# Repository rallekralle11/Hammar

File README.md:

This board is untested. Make at your own risk.

Based on the ESP wroom-32E, which also enables wifi communication.
Total size is only 97,5x55mm

Still in development, but should be functional. Use with the fysetc E4 config in marlin

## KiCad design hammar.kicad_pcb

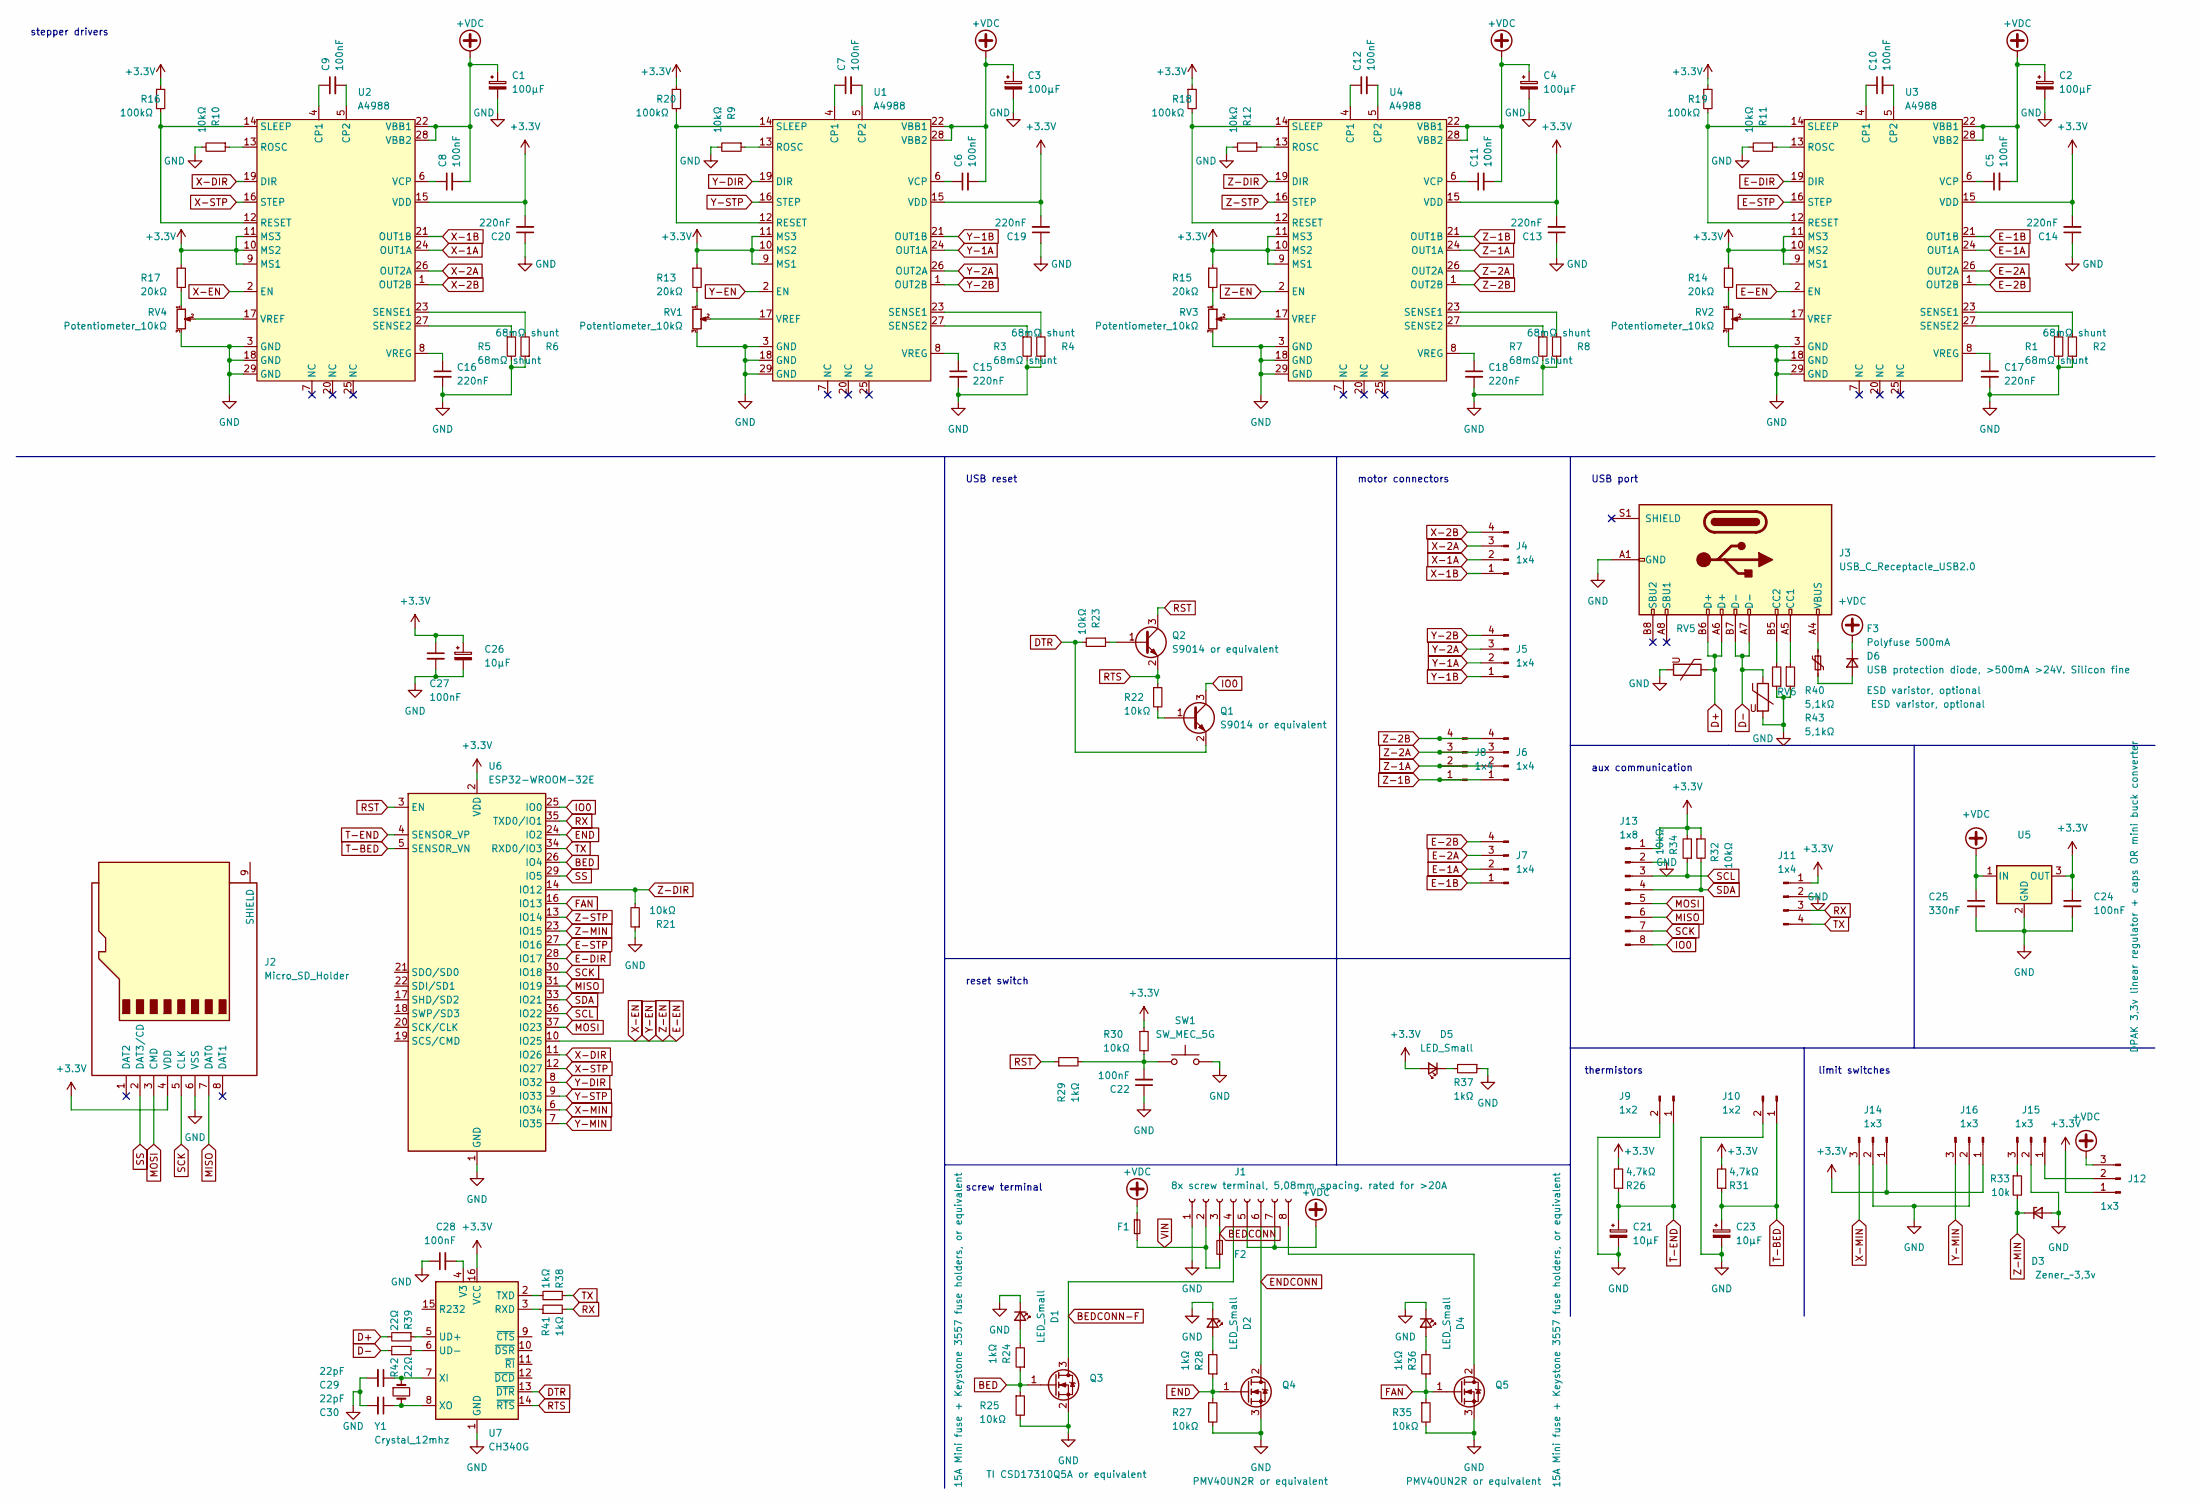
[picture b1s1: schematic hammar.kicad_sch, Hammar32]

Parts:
C1, C2, C3, C4: 100µF; CP_Elec_6.3x4.9
C5, C6, C7, C8, C9, C10, C11, C12, C22, C24, C27, C28: 100nF; C_0603_1608Metric
C13, C14, C15, C16, C17, C18, C19, C20: 220nF; C_0603_1608Metric
C21, C23, C26: 10µF; C_0805_2012Metric
C25: 330nF; C_0603_1608Metric
C29, C30: 22pF; C_0603_1608Metric
D1, D2, D4, D5: LED_Small; LED 0603 reverse mount
D3: Zener_~3,3v; D_SOD-323
D6: USB protection diode, >500mA >24V. Silicon fine; D_SOD-323
F1, F2: 15A Mini fuse + Keystone 3557 fuse holders, or eq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; mini fuse sep
F3: Polyfuse 500mA; Fuse_1206_3216Metric
J1: 8x screw terminal, 5,08mm spacing. rated for >20A; TerminalBlock_bornier-6_P5.08mm
J2: Micro_SD_Holder; microSD
J3: USB_C_Receptacle_USB2.0; USB_C_Receptacle_HRO_TYPE-C-31-M-12
J4, J5, J6, J7, J8, J11: 1x4; PinHeader_1x04_P2.54mm_Vertical
J9, J10: 1x2; PinHeader_1x02_P2.54mm_Vertical
J12, J14, J15, J16: 1x3; PinHeader_1x03_P2.54mm_Vertical
J13: 1x8; PinHeader_1x08_P2.54mm_Vertical
Q1, Q2: S9014 or equivalent; SOT-23
Q3: TI CSD17310Q5A or equivalent; 8-VSONP (5x6)
Q4, Q5: PMV40UN2R or equivalent; SOT-23
R1, R2, R3, R4, R5, R6, R7, R8: 68mΩ shunt; R_0603_1608Metric
R9, R10, R11, R12, R21, R22, R23, R25, R27, R30, R32, R34, R35: 10kΩ; R_0603_1608Metric
R13, R14, R15, R17: 20kΩ; R_0603_1608Metric
R16, R18, R19, R20: 100kΩ; R_0603_1608Metric
R24, R28, R29, R36, R37, R38, R41: 1kΩ; R_0603_1608Metric
R26, R31: 4,7kΩ; R_0603_1608Metric
R33: 10k; R_0603_1608Metric
R39, R42: 22Ω; R_0603_1608Metric
R40, R43: 5,1kΩ; R_0603_1608Metric
RV1, RV2, RV3, RV4: Potentiometer_10kΩ; Potentiometer_Bourns_3314J_Vertical
RV5, RV6: ESD varistor, optional; R_0603_1608Metric
SW1: SW_MEC_5G; SW_PUSH_6mm
U1, U2, U3, U4: A4988; QFN-28-1EP_5x5mm_P0.5mm_EP3.35x3.35mm
U5: DPAK 3,3v linear regulator + caps OR mini buck co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; mini BUCK
U6: ESP32-WROOM-32E; ESP32-WROOM-32
U7: CH340G; SOIC-16_3.9x9.9mm_P1.27mm
Y1: Crystal_12mhz; Crystal_SMD_ECS_CSM3X-2Pin_7.6x4.1mm

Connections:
+3.3V: C13.2, C14.2, C19.2, C20.2, C24.1, C26.1, C27.1, D5.2 (A), J2.4 (VDD), J11.1, J12.1, J13.1, J14.1, J16.1, R13.1, R14.1, R15.1, R16.1, R17.1, R18.1, R19.1, R20.1, R26.2, R30.1, R31.2, R32.1, R34.2, U1.9 (MS1), U1.10 (MS2), U1.11 (MS3), U1.15 (VDD), U2.9 (MS1), U2.10 (MS2), U2.11 (MS3), U2.15 (VDD), U3.9 (MS1), U3.10 (MS2), U3.11 (MS3), U3.15 (VDD), U4.9 (MS1), U4.10 (MS2), U4.11 (MS3), U4.15 (VDD), U5.3 (OUT), U6.2 (VDD), U7.16 (VCC)
+VDC: C1.1, C2.1, C3.1, C4.1, C5.2, C6.2, C8.2, C11.2, C25.1, D6.1 (K), F1.1, J1.5, J1.7, J12.3, U1.22 (VBB1), U1.28 (VBB2), U2.22 (VBB1), U2.28 (VBB2), U3.22 (VBB1), U3.28 (VBB2), U4.22 (VBB1), U4.28 (VBB2), U5.1 (IN)
BED: Q3.1 (G), R24.1, R25.1, U6.26 (IO4)
BEDCONN: F2.1, J1.3
BEDCONN-F: J1.4, Q3.3 (D)
D+: J3.A6 (D+), J3.B6 (D+), R39.2, RV5.1
D-: J3.A7 (D-), J3.B7 (D-), R42.1, RV6.1
DTR: Q1.2 (E), R23.2, U7.13 (~DTR)
E-1A: J7.2, U3.24 (OUT1A)
E-1B: J7.1, U3.21 (OUT1B)
E-2A: J7.3, U3.26 (OUT2A)
E-2B: J7.4, U3.1 (OUT2B)
E-DIR: U3.19 (DIR), U6.28 (IO17)
E-EN: U1.2 (EN), U2.2 (EN), U3.2 (EN), U4.2 (EN), U6.10 (IO25)
E-STP: U3.16 (STEP), U6.27 (IO16)
END: Q4.1 (G), R27.1, R28.1, U6.24 (IO2)
ENDCONN: J1.6, Q4.2 (D)
FAN: Q5.1 (G), R35.1, R36.1, U6.16 (IO13)
IO0: J13.8, Q1.3 (C), U6.25 (IO0)
MISO: J2.7 (DAT0), J13.6, U6.31 (IO19)
MOSI: J2.3 (CMD), J13.5, U6.37 (IO23)
unnamed: C5.1, U3.6 (VCP)
unnamed: C6.1, U1.6 (VCP)
unnamed: C7.1, U1.4 (CP1)
unnamed: C7.2, U1.5 (CP2)
unnamed: C8.1, U2.6 (VCP)
unnamed: C9.1, U2.4 (CP1)
unnamed: C9.2, U2.5 (CP2)
unnamed: C10.1, U3.4 (CP1)
unnamed: C10.2, U3.5 (CP2)
unnamed: C11.1, U4.6 (VCP)
unnamed: C12.1, U4.4 (CP1)
unnamed: C12.2, U4.5 (CP2)
unnamed: C15.1, U1.8 (VREG)
unnamed: C16.1, U2.8 (VREG)
unnamed: C17.1, U3.8 (VREG)
unnamed: C18.1, U4.8 (VREG)
unnamed: C28.2, U7.4 (V3)
unnamed: C29.1, U7.7 (XI), Y1.1
unnamed: C30.1, U7.8 (XO), Y1.2
unnamed: D1.2 (A), R24.2
unnamed: D2.2 (A), R28.2
unnamed: D4.2 (A), R36.2
unnamed: D5.1 (K), R37.2
unnamed: D6.2 (A), F3.2
unnamed: F3.1, J3.A4 (VBUS), J3.A9 (VBUS), J3.B4 (VBUS), J3.B9 (VBUS)
unnamed: J1.8, Q5.2 (D)
unnamed: J3.A5 (CC1), R43.1
unnamed: J3.B5 (CC2), R40.2
unnamed: J12.2, J15.1
unnamed: J15.3, R33.1
unnamed: Q1.1 (B), R22.2
unnamed: Q2.1 (B), R23.1
unnamed: R1.1, U3.27 (SENSE2)
unnamed: R2.2, U3.23 (SENSE1)
unnamed: R3.1, U1.27 (SENSE2)
unnamed: R4.2, U1.23 (SENSE1)
unnamed: R5.1, U2.27 (SENSE2)
unnamed: R6.2, U2.23 (SENSE1)
unnamed: R7.1, U4.27 (SENSE2)
unnamed: R8.2, U4.23 (SENSE1)
unnamed: R9.1, U1.13 (ROSC)
unnamed: R10.1, U2.13 (ROSC)
unnamed: R11.1, U3.13 (ROSC)
unnamed: R12.1, U4.13 (ROSC)
unnamed: R13.2, RV1.1
unnamed: R14.2, RV2.1
unnamed: R15.2, RV3.1
unnamed: R16.2, U2.12 (RESET), U2.14 (SLEEP)
unnamed: R17.2, RV4.1
unnamed: R18.2, U4.12 (RESET), U4.14 (SLEEP)
unnamed: R19.2, U3.12 (RESET), U3.14 (SLEEP)
unnamed: R20.2, U1.12 (RESET), U1.14 (SLEEP)
unnamed: R38.2, U7.2 (TXD)
unnamed: R39.1, U7.5 (UD+)
unnamed: R41.1, U7.3 (RXD)
unnamed: R42.2, U7.6 (UD-)
unnamed: RV1.2, U1.17 (VREF)
unnamed: RV2.2, U3.17 (VREF)
unnamed: RV3.2, U4.17 (VREF)
unnamed: RV4.2, U2.17 (VREF)
RST: Q2.3 (C), R29.1, U6.3 (EN)
RTS: Q2.2 (E), R22.1, U7.14 (~RTS)
RX: J11.3, R41.2, U6.35 (TXD0/IO1)
SCK: J2.5 (CLK), J13.7, U6.30 (IO18)
SCL: J13.3, R34.1, U6.36 (IO22)
SDA: J13.4, R32.2, U6.33 (IO21)
SS: J2.2 (DAT3/CD), U6.29 (IO5)
T-BED: C23.1, J10.1, R31.1, U6.5 (SENSOR_VN)
T-END: C21.1, J9.1, R26.1, U6.4 (SENSOR_VP)
TX: J11.4, R38.1, U6.34 (RXD0/IO3)
VIN: F1.2, F2.2, J1.2
X-1A: J4.2, U2.24 (OUT1A)
X-1B: J4.1, U2.21 (OUT1B)
X-2A: J4.3, U2.26 (OUT2A)
X-2B: J4.4, U2.1 (OUT2B)
X-DIR: U2.19 (DIR), U6.11 (IO26)
X-MIN: J14.3, U6.6 (IO34)
X-STP: U2.16 (STEP), U6.12 (IO27)
Y-1A: J5.2, U1.24 (OUT1A)
Y-1B: J5.1, U1.21 (OUT1B)
Y-2A: J5.3, U1.26 (OUT2A)
Y-2B: J5.4, U1.1 (OUT2B)
Y-DIR: U1.19 (DIR), U6.8 (IO32)
Y-MIN: J16.3, U6.7 (IO35)
Y-STP: U1.16 (STEP), U6.9 (IO33)
Z-1A: J6.2, J8.2, U4.24 (OUT1A)
Z-1B: J6.1, J8.1, U4.21 (OUT1B)
Z-2A: J6.3, J8.3, U4.26 (OUT2A)
Z-2B: J6.4, J8.4, U4.1 (OUT2B)
Z-DIR: R21.2, U4.19 (DIR), U6.14 (IO12)
Z-MIN: D3.1 (K), R33.2, U6.23 (IO15)
Z-STP: U4.16 (STEP), U6.13 (IO14)

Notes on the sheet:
USB reset
USB port
reset switch
limit switches
stepper drivers
thermistors
aux communication
motor connectors
screw terminal

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
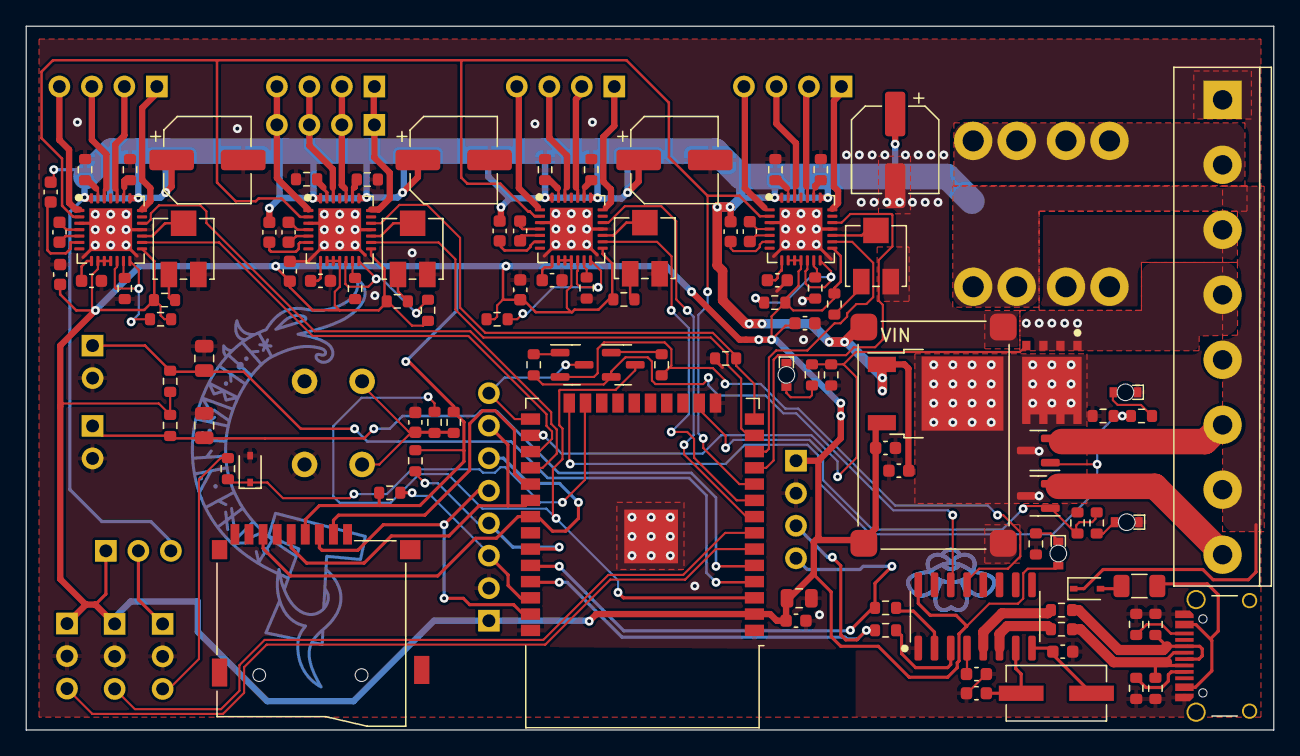
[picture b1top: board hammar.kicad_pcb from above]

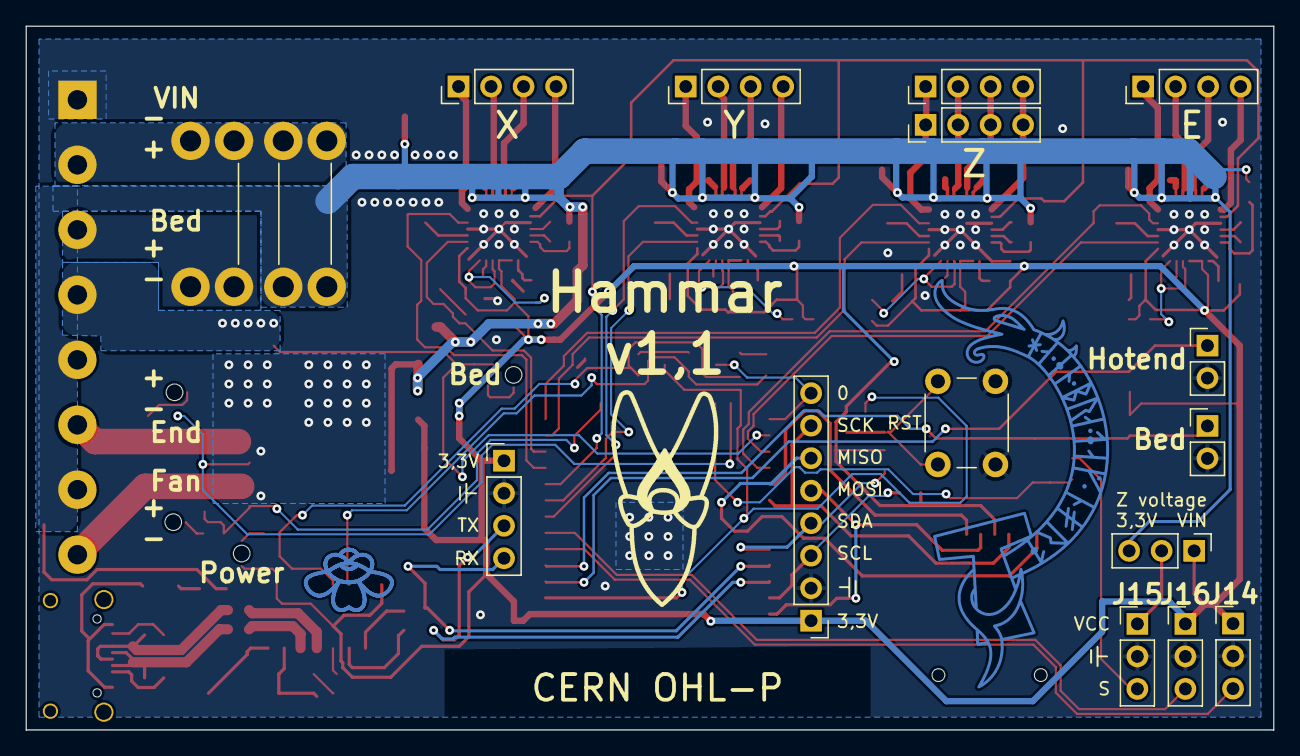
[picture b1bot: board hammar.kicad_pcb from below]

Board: 2 copper layers, 97.5 x 55.0 mm, 118 parts (16 on the bottom side), 115 nets.

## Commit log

2022-11-22 initial
2022-11-22 name changes
2022-11-24 Redesign
2022-11-24 changed designators and updated BOM
2022-11-24 little fix
2022-11-24 updated BOM
2022-11-24 updated bom++
2022-11-24 slight reference update
2022-11-25 added 3D models
2022-11-25 got rid of a couple unused files
2022-11-25 BOM++
2022-11-26 lil update
2022-11-30 fixed reference designators
2022-12-09 replaced oscillator with crystal
2022-12-11 removed possibly problematic trace
2022-12-14 can't remember
2023-01-06 Update fp-info-cache

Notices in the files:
hammar.kicad_pcb:
CERN OHL-P
